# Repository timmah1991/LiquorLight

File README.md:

# LiquorLight

Simple, glowing light that installs at the top of an emptied glass bottle for interesting visual effect.

Project includes a circuit board and a manufactured plastic enclosure. The enclosure for this project was designed for additive manufacturing, and can easily be retrofitted for injection molding by adding a few chamfers and adjusting extrusion angles.

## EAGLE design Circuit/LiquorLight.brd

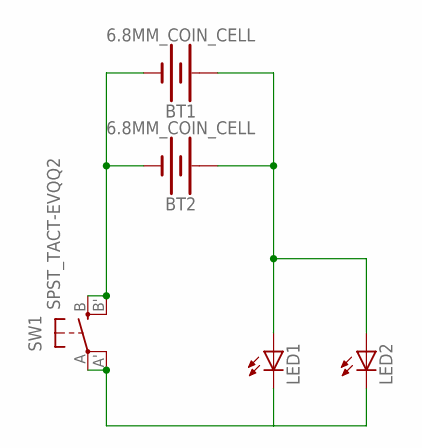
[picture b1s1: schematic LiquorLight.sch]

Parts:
BT1, BT2: 6.8MM_COIN_CELL; BATTCON-6.8MM
LED1, LED2: LED3MM
SW1: SPST_TACT-EVQQ2; EVQ-Q2

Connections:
unnamed: BT1.+, BT2.+, LED1.A, LED2.A
unnamed: LED1.K (C), LED2.K (C), SW1.A, SW1.A' (P1)
unnamed: BT1.-, BT2.-, SW1.B (S), SW1.B' (S1)

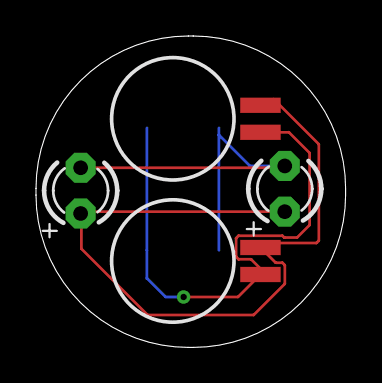
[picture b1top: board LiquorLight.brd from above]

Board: 2 copper layers, 17.2 x 17.3 mm, 5 parts (1 on the bottom side), 3 nets.

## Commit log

2019-02-26 adding stl, schematic and screenshots
2019-02-26 .DS_Store banished!

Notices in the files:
parts and their libraries:
SparkFun-Batteries: Licensing: Creative Commons ShareAlike 4.0 International - https://creativecommons.org/licenses/by-sa/4.0
